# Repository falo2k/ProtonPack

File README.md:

# Teensy Based Proton Pack Electronics
This is my implementation of the electronics for a Ghostbusters Proton Pack.  It uses a Teensy microcontroller in both parts of the kit (Pack and Wand) and communicates between them over 4 wires (power + serial).  For now I have kept it to a simple movie implementation with some additions - overheating and music playback.  I've added two features that are a bit unusual:
- An OLED display in the rear box on the wand is used for managing volume control and track selection, in conjunctions with a rotary encoder (push/turn) in the front knob.
- A [bluetooth receiver](./Images/bluetooth.jpg) can be turned on for playback of anything not available on the SD card.  The module I'm using will mix the stereo audio down to mono for a single pack, but comes as a pair for True Wireless Stereo.  The other board will be in a friend's pack so we can use the packs as a complete speaker set.
  
It is designed to fit inside the 3D printed pack available [here - the Q-Pack](https://github.com/mr-kiou/q-pack).  It's been developed for a Mk3 pack - I will review it at some point in the future for Mk4 compatability.

## Software
The code is set up as a VS solution/project set using [Visual Micro](https://www.visualmicro.com/), but you can tweak this to your preferred environment.  There are three core files:
- Wand.ino for the Wand sketch
- Pack.ino for the Pack sketch
- ProtonPackCommon.h which is used by both for some shared enums, timers, etc.
  
The Wand sketch does all state management, and will update the Pack sketch as necessary over serial.  If you want to tweak speeds, animations, direction of switches, etc. then you should find the right data to change either above the setup() functions in each file, or within the common header.
  
You'll need the libraries listed in the section below.

### Libraries
[minIni for Arduino](https://github.com/lipoyang/minIni4Arduino) - Config file saving/loading with the SD card  
[LCDGFX](https://github.com/lexus2k/lcdgfx/) - Drives the OLED display  
[CmdMessenger](https://github.com/thijse/Arduino-CmdMessenger) - Manages serial connection between both boards with callbacks  
[Encoder](https://github.com/PaulStoffregen/Encoder) - Converts rotary encoder inputs to movement  
[HT16K33](https://github.com/jonpearse/ht16k33-arduino) - Basic library for controlling the LED matrix backpack/bargraph.  
[NeoPixel](https://github.com/adafruit/Adafruit_NeoPixel) - The Adafruit NeoPixel library.  Considered using FastLED, but as I had GRBW LEDs in stock (and wanted them for some parts) I stuck with the Adafruit library.  
[TimerEvent](https://github.com/cygig/TimerEvent) - A library for managing timing of updates (helping to banish unnecessary delay() calls)  
[Switch](https://github.com/avandalen/avdweb_Switch) - Primarily used for the debouncing and callback features for switches.  Detects events for pressing, holding, and releasing.  

### Pack Operation
Once power is on to both boards, they will start up in the state determined by the current switch positions, so you can switch straight into music mode if you want.  If the pack is powered without a wand connected, it will enter bluetooth mode after 5 seconds.  When both are connected, and the Activate switch is in the off position, a top light on the wand will pulse a faint blue to remind you that your battery is still connected!  

**Act Switch on Left Box**  
- This toggles the pack power-up for both movie and music mode.

**Lower Switch Next to Bargraph**  
- In movie mode this toggles whether or not the overheat warning will kick in after a period of time and then move to venting after further warning.  If off, firing will continue indefinitely.  
- In music mode, this is used to toggle the Bluetooth module on, which will then stop any playback from the SD card.

**Upper Switch Next to Bargraph**  
- This switches between movie mode (off) and music mode (on)

**Int Button on Left Box**  
- In movie mode, this will cause the pack to fire while held.  
- In music mode a single press will act as a play/pause button, while a long press will move to the next track in the list.

**Tip Button**  
- In movie mode, this will cause the pack to fire while held.  If single pressed, it will cause a venting routing to kick off.  
- In music mode a single press will act as a stop button, while a long press will move to the previous track in the list.

**Pack Crank Knob**  
- Connected to an encoder, this independently controls volume of the pack when held and turned.

**Pack Ion Switch**  
- Currently unused.

### OLED Menu System
A long press on the Wand encoder will activate the menu (to avoid accidental bumps).  While active, a long press will also cancel the menu.  The menu has an automatic timeout so will not stay open indefinitely.  Single click to select / confirm menu items

Currently there these features for control:  
1. **Volume**: This changes the volume of the amplifier in the pack via i2c.  This will update as you turn the knob.  
2. **Track Change**: This lets you select the extact track you want queued up for playback from the SD card (if enabled).  Single click to confirm the selection, or long press to cancel.  Selecting a new track while one is playing will cause the new track to start immediately.  Note that using the next/prev track shortcuts on the INT/TIP buttons will display the new track name in the display.  
3. **Overheat/Warning Time**: For overheat mode, this will change the timings for how long until the warning starts (overheat) and how long the warning lasts before forced venting (warning).  
4. **Load/Save Config**: This will load or save the volume, track, and timing configuration to a file on the SD card.  This is loaded as the default when the pack is first powered  
  
A long press in any menu item should take you back up one level.  
  
[Demo video here](https://youtu.be/a6icHuyzO3Q)
  
### Lights Colours & Lenses
The light colours I've used in my code were chosen to work with the lenses and printed hats I'm using.  I would recommend testing against your own installation and tweaking them accordingly.  My setup is:  
- Power cell is a layer of frosted acrylic + a top layer of blue acrylic (so lighting aims to send green and blue only)  
- Cyclotron lenses are just frosted acrylic so I can do any colour.  They are mounted over printed reflectors lined with a red chrome vinyl layer to give them a red tint when off.  
- For the wand LED covers the slo blo is red, tip hat is orange, front shelf is opaque white, top front is clear, and top rear is orange.  

### Future Plans
- General code refactoring where I've got a few inconsistent approaches.  Tidy up method signatures a bit to be consistent with ordering of arguments, remove TimerEvent as I've ended up with some custom implementations of the same principle so should be consistent.  
- Some pin headers in the pack are already spare to support adding a smoke machine to the pack at a later date for venting (marked as IO2 on the PCB).  This should be easy to add triggers in software at the appropriate state changes.  I've seen some interesting looking i2c relay boards or i2c IO expanders out there as alternative options if I want more granular control over pump, smoke, fan for the effects.  
- Alternative lighting schemes, sounds, animations, etc. can be added relatively easily.  Switching would probably be done with additional menu items through the OLED controls.  
- I'll play with adding more granular volume control, again through the menu, to individually tweak the volume of SFX, Music, and Bluetooth channels.  This may turn out to be unnnecessary given the sounds should already be balanced and bluetooth volume should be handled by the device sending audio.  
- The Ion Switch input currently doesn't do anything.  I may use this as either a hard or soft toggle for any future smoke effects.  
- Review the PCBs for other layout options.  Now I've got my own wiring in, I might see some better positioning for connectors, consider breakout boards, etc.  
- Consider either including an isolated converter in the BOM and as part of existing PCBs, or a breakout depending on power requirements for the smoke system.
- Consider a better menu system, and make **all** configurable settings switchable in software.  That would reduce the need for any trial and error with USB cables attached and would allow for all tweaking of things like switch directions, cyclotron spin directions, etc. possible through the OLED menu.  Could even then distribute just the binaries of the firmware for busters who don't want to go anywhere near an IDE.  
- I'd like to add USB panel breakouts onto the motherboard and somewhere on the wand for access to the internal devices without needing to take my shell off.  If I can somehow make the SD card accessible as mass storage when connected as well then so much the better. 

## Music Tracks
I've removed the music tracks from this repository, but you can see which ones I had loaded in [ProtonPackCommon.h](./Teensy/ProtonPackCommon/src/ProtonPackCommon.h).  You can replace these with your own copies, or adapt the header file to manage your own.  I used 16 bit 44.1khz wave files downmixed to mono as I only have a single speaker setup in the pack.  I believe the audio board does support MP3 with some overhead, but there's so much space on a SD card that I didn't care.  Audacity was used for file processing because it's great.  
  
If you want to add more music tracks to the pack, bearing in mind that it might take a while to change them given the simple scrolling menu, then you can update the arrays in ProtonPackCommon.h to reference them.  Make sure to update the track count as well.  
  
## Hardware
### BOM
Where I can remember it, I've listed the Equipment used and links to purchase below.  You may find other sources are better for availability (Mouser, Digikey, etc.).  As with all of these types of projects, it depends exactly how you're planning to mount your electronics, so I'd advise thinking about your layout before purchasing.  I'm assuming I don't need to go into tools and wire here, that should be a given.  A decent soldering iron is a must, and I have to say how much I'm loving my [Pinecil](https://www.pine64.org/pinecil/), and also the best helping hands I've ever used, the [Omnifixo](https://omnifixo.com/en-gb).  

**Controllers**  
 2 x [Teensy 4.0](https://www.pjrc.com/store/teensy40.html)  
 1 x [Teensy Audio Board Rev D](https://www.pjrc.com/store/teensy3_audio.html)  
 1 x [Teensy Stacking Header Kit](https://www.adafruit.com/product/3883).  For the audio board to stack on the Teensy 4.0.  This was the easiest source of 14 pin stackable headers I could find.  If not using PCBs then you may just stick with non-stacking headers here.  
 4 x [14x1R Pins](https://www.pjrc.com/store/header_14x1.html) for the Teensy boards  
 4 x [14x1R Socket Headers](https://www.pjrc.com/store/socket_14x1.html) for the PCBs  
 1 x [5x2R Socket Header](https://www.amazon.co.uk/Double-Female-Straight-Header-Socket-Black/dp/B00R1LKZOM/ref=sr_1_5?crid=2BQW1XCGHFEJU&keywords=2r+5+header&qid=1682349085&sprefix=2r+5+he%2Caps%2C120&sr=8-5) for the PCB connection to the audio inputs/outputs on the board  
 1 x Micro SD Card for the Audio Adapter.  See the [Audio Adapter product page](https://www.pjrc.com/store/teensy3_audio.html#:~:text=video%20for%20details.-,Recommended%20SD%20Card,-Most%20SD%20cards) for up to date recommendations.  Not much is stored on here so you can get away with a fairly small card, but if you want to load more songs on YMMV.  

**Premade Boards**  
1 x [Adafruit 16x8 LED Matrix Driver Backpack - HT16K33 Breakout](https://www.adafruit.com/product/1427) for driving the bargraph.  
1 x [DFRobot Mosfet Controller DFR0457](https://wiki.dfrobot.com/Gravity__MOSFET_Power_Controller_SKU__DFR0457) to switch the bluetooth board  
1 x [Adafruit 20W Class D Amplifier](https://www.adafruit.com/product/1752)  
1 x [Bluetooth Audio Board](https://www.aliexpress.com/item/1005004753541997.html). Comes as a wireless stereo pair.  

**Buttons and Switches**  
3 x [2 Position MTS102 mini toggle switches](https://www.amazon.co.uk/gp/product/B01BWL7Z44/) for wand  
1 x [Black Off/On SPST Momentary switch](https://www.amazon.co.uk/gp/product/B00TXNXU4S)  
1 x [Red Off/On SPST Momentary switch](https://www.amazon.co.uk/gp/product/B008ZYE9LY)  
2 x [EC11 Rotary Encoder with Switch](https://www.ebay.co.uk/sch/i.html?_from=R40&_trksid=p2380057.m570.l1313&_nkw=ec11+rotary+encoder&_sacat=0) for the pack (crank) and wand (top / front knob).  Lengths will depend on your shells, and where you're placing the encoder.  
  
Ion switches can be picked up on Etsy.  
  
I also use some of [these](https://www.digikey.co.uk/en/products/detail/e-switch/100DP1T1B1M1QEH/378867) to switch on/off and choose charging vs electronics power for my internally mounted [Talentcell battery](https://talentcell.com/lithium-ion-battery/12v/yb1206000-usb.html).

**LEDs**  
You may want to do your own LEDs.  Numbers and type can be varied in the code, though I haven't allowed for cyclotron LEDs that are more than a single addressable LED in a chain.  You may want to use the 7 LED jewels, though I found they were unnecessary for brightness and just ramped up power consumption for the sake of it.  
1 x [144LEDs/m SK6812 RGBW Strip](https://www.aliexpress.com/item/32476317187.html?spm=a2g0o.order_list.order_list_main.5.74871802yO2AMH).  144 LEDs/m is just enough density to give you 15 LEDs in the Power Cell.  You can get a minimum length if you like.  
13+ x [SK6812 RGBW Chips](https://www.aliexpress.com/item/1005002509850925.html?spm=a2g0o.order_list.order_list_main.29.74871802yO2AMH) which I use in the wand, pack vent, and for the cyclotron.  Worth getting some spares in case you fry one.  
1 x [RGBW LED jewel](https://www.aliexpress.com/item/32825068416.html?spm=a2g0o.order_list.order_list_main.56.74871802yO2AMH) for the barrel light  
1 x [28 Segment Bar Graph](http://www.barmeter.com/download/bl28-3005sda04y.pdf).  Sourcing for this always ends up out of date, so hunt around Aliexpress or try asking on one of the FB groups.  Note that there are two versions of this bargraph, a common anode and common cathode version.  My code is designed for the [BL28-3005SDK04Y](./Images/bargraphwiring.jpg) model (note the A or K in the model name differentiating them).  It can be adapted for the other by simply changing the array mapping in the common header to point to the correct row/column references for your model.  

**Capacitors and Resistors**  
4 x 4.7K Ohm Resistors for pullups on the Teensy i2c lines  
6 x 220 Ohm Resistors for neopixel data inputs  
2 x 100 uF Capacitors for neopixel power inputs (these may not be necessary depending on the pixels you're using - I'm keeping them in as they don't harm)  

**Connectors (for PCB / wiring)**  
Source these where you like depending on how many you need / want for other projects.  I tend to buy bulk lots from AliExpress.  You can count up the exact number you need, but I always find I need more so I'll leave them open ended :)  
- [JST-XH connectors and headers](https://www.digikey.co.uk/en/product-highlight/j/jst/xh-series-connectors) for the boards and cables (2,3,4 pin)  
- [Screw terminal blocks](https://www.digikey.co.uk/en/products/detail/phoenix-contact/1729018/260604) (2 pin, 5mm pitch) 
- [Dupont connectors](https://www.amazon.co.uk/dupont-connectors/s?k=dupont+connectors)
- [JST-SM wire to wire connectors](https://www.amazon.co.uk/Aussel-Connector-Housing-Assortment-Kit-560PCS-2-5mm-JST-SM-Connector-560PCS/dp/B0716JMHNJ/ref=sr_1_5?crid=1V0JLS666ZR6J&keywords=jst+sm+kit&qid=1682347520&sprefix=jst+sm+kit%2Caps%2C67&sr=8-5) for  (handy locking wire to wire options)  
- [JST-PH connectors](https://www.amazon.co.uk/RUNCCI-YUN-540Pcs-Connector-Housing-Adapter/dp/B092LWQJHN/ref=sr_1_7?crid=V8F2IT2RMUFS&keywords=jst%2Bph%2Bkit&qid=1682347555&sprefix=jst%2Bph%2Bkit%2Caps%2C65&sr=8-7&th=1) (2,3 pin) for some of the smaller connectors on the DFRobot boards and the bluetooth board  
- An assortment of [Wago221s](https://www.amazon.co.uk/s?k=wago+221) because they're brilliant for patching cables together with quick release  
- [2 Pairs of 4 pin aviation connectors](https://www.amazon.co.uk/gp/product/B09WXZNKXN/ref=ppx_yo_dt_b_search_asin_title?ie=UTF8&psc=1) which I use to carry the serial/power to and from the wand while allowing a quick release.

**Other**  
2 x [74AHCT125 Level Shifters](https://www.adafruit.com/product/1787) for driving the Neopixels as the Teensy uses 3.3V logic.  You may get away without these, but better safe than sorry.  
2 x [14 Pin IC Sockets](https://www.digikey.co.uk/en/products/detail/cnc-tech/245-14-1-03/3441580) for mounting the above into the PCBs (or you can just solder them in).  
1 x [0.91-inch OLED Display SSD1306](https://www.amazon.co.uk/gp/product/B07V8B3LSR)
1 x [M6 Thumb Nut](https://www.aliexpress.com/item/1005003320281166.html) for the top knob on the wand.  I drilled out a 2.5 mm hole in the side, tapped it for M3 and used a grub screw to attach it to an encoder.  The top is capped with a cut-off and glued countersunk bolt head.

### PCBs
I have created a couple of PCBs to make installation neater in a Q-Pack.  I've shared the production files in the PCBs folder for use with [JLCPCB](https://jlcpcb.com/) - note that they have a placeholder JLCJLCJLCJLC text on the rear silkscreen so you can use the "Specify a location" option in JLC for order numbering.  I used Altium Circuitmaker to create these, so it's hard to share a useful copy of them.  I plan at some point to migrate these to KiCad but that requires time to learn KiCad.  It'll probably happen when I start working on a better belt gizmo :)  
  
The folder also contains STLs to mount the boards and keep the solder joins clear of the mounting surface.  For the Wand, it is just a spacer - the board is designed to fit along the handle side of the Mk3 Q-Pack, using the external M3 bolt to secure it with a nut internally.  This should position the serial/power connections for the handle exit, but leave enough space for an encoder to run through the top/front knob if desired.  For the pack, it's a backer designed to have M3x5x4 heat sets (standard size used in [Vorons](https://www.vorondesign.com/)) added to the holes so the board can be attached and removed easily with M3 bolts.  The backer can then be secured in place to the motherboard with VHB tape.  It should be slim enough to fit underneath the booster box of the Mk3 Q-Pack.  

Lastly, the current version did not take into account the 3mm inset on the box lid.  I have added an alternative STL for this into the folder, but will refactor the PCBs when I redo them in the future.  My STL for the lid also changes some hole sizes as I'm using M3 + heat inserts to attach to the box, and M4 for metal V-Hook/S-Hook connectors.  

Note that the wand board already contains the components necessary for motor switching (transistor, diode, etc.), whereas the pack board offers simple HI/LO pin output for bluetooth and vent switching (with reference voltage).  This is to make it agnostic to how you want to do your switching for devices not directly powered by the Teensy.  If you don't want to build your own circuits, there are some good pre-packaged boards out there for relay switching or transistor switching.  DFRobot or Adafruit are good places to look.  

Note: Jigs - space for through hole components, but I wouldn't rely on them, or do them on a second pass.  They're often easier to do after the sockets, just bending the legs before soldering.  Jig accuracy will depend on how well tuned your printer is for dimensions, corners, etc. so some cleanup with a knife may be required if you wish to use them.  I find they fit snug (post any shrinkage) printing ABS on a Voron.

*Revision 1.0:* Initial release of boards  
*Revision 1.1:* Pack board updated to move Audio Board output pin.  I made a mis-reading of the schematic, and only the pins nearest the Teensy pins are connected to L/R out.  Temporarily solder bridged on my v1.0 boards.  
*Revision 2.0:* Wand board migrated to KiCad and updated to better fit in stock Q-Pack wand shell.  Updated the PCB to support the Teensy 4.0 as the LC is now EOL.  Added additional headers to board for USB data breakout (via pogo pins), for connecting a hall effect sensor for barrel state sensing, and for controlling a rumble motor (5V).  Generally re-jigged the layout, with the priority being having the teensy USB port facing upwards for access with the wand baseplate removed.

### Power
I've left supplying the 5V power to the boards to the individual user.  You can take a feed directly from a Talentcell 5V output or use a common buck converter, but either of these may introduce some noise into the audio.  Your mileage with this may vary.  I got myself some [isolated dc-dc converters](https://www.digikey.co.uk/en/products/detail/mornsun-america-llc/VRB1205S-6WR3/16348304) to step down my 12V talentcell battery and avoid noise issues going to the amp.  6W is overspecced - in my testing, the setup draws at most 0.6A at its busiest time when in the overheat warning sequence.  They're working [well for me so far](./Images/powerboard.jpg).

## Useful Models
I'm slowly going over my library of replacement parts and jigs that I've made over the course of this build and exporting them into the [STLs](./STLs/) folder (and where appropriate I'll feed some back as PRs for the q-pack).  Things like board mounts are generally reusable either with my PCBs or the off-the-shelf boards listed above.  Some bits I've made are very specific to my build so probably not of interest to others.  Have a play with Fusion 360 - you'll both love and hate yourself as a result, but you'll be too far down the rabbit hole of making to notice :)  

If you see any others I'm using in photos and want to get hold of them, let me know.  

## Thanks
A huge thanks to everyone over on the [Arduino for Ghostbusters Props](https://www.facebook.com/groups/1187612118706042/) Facebook group.  Special shout outs to:  
- Chris Rossi for steering me towards the Teensy in the first place
- Kevin Delcourt for his excellent github documentation.  Inspired me to take a different approach to fixing the top knob to the encoder!
- Quentin Machiels and Taco Belli over at [3D Printed Ghostbusters Props](https://www.facebook.com/groups/3DprintedGBprops/), without whom I would not have a pack to build this into
- [Mike Simone](https://github.com/MikeS11/ProtonPack) and [CountDeMonet](https://github.com/CountDeMonet/ArduinoProtonPack) for their implementations.  Both have steered hardware and software choices.

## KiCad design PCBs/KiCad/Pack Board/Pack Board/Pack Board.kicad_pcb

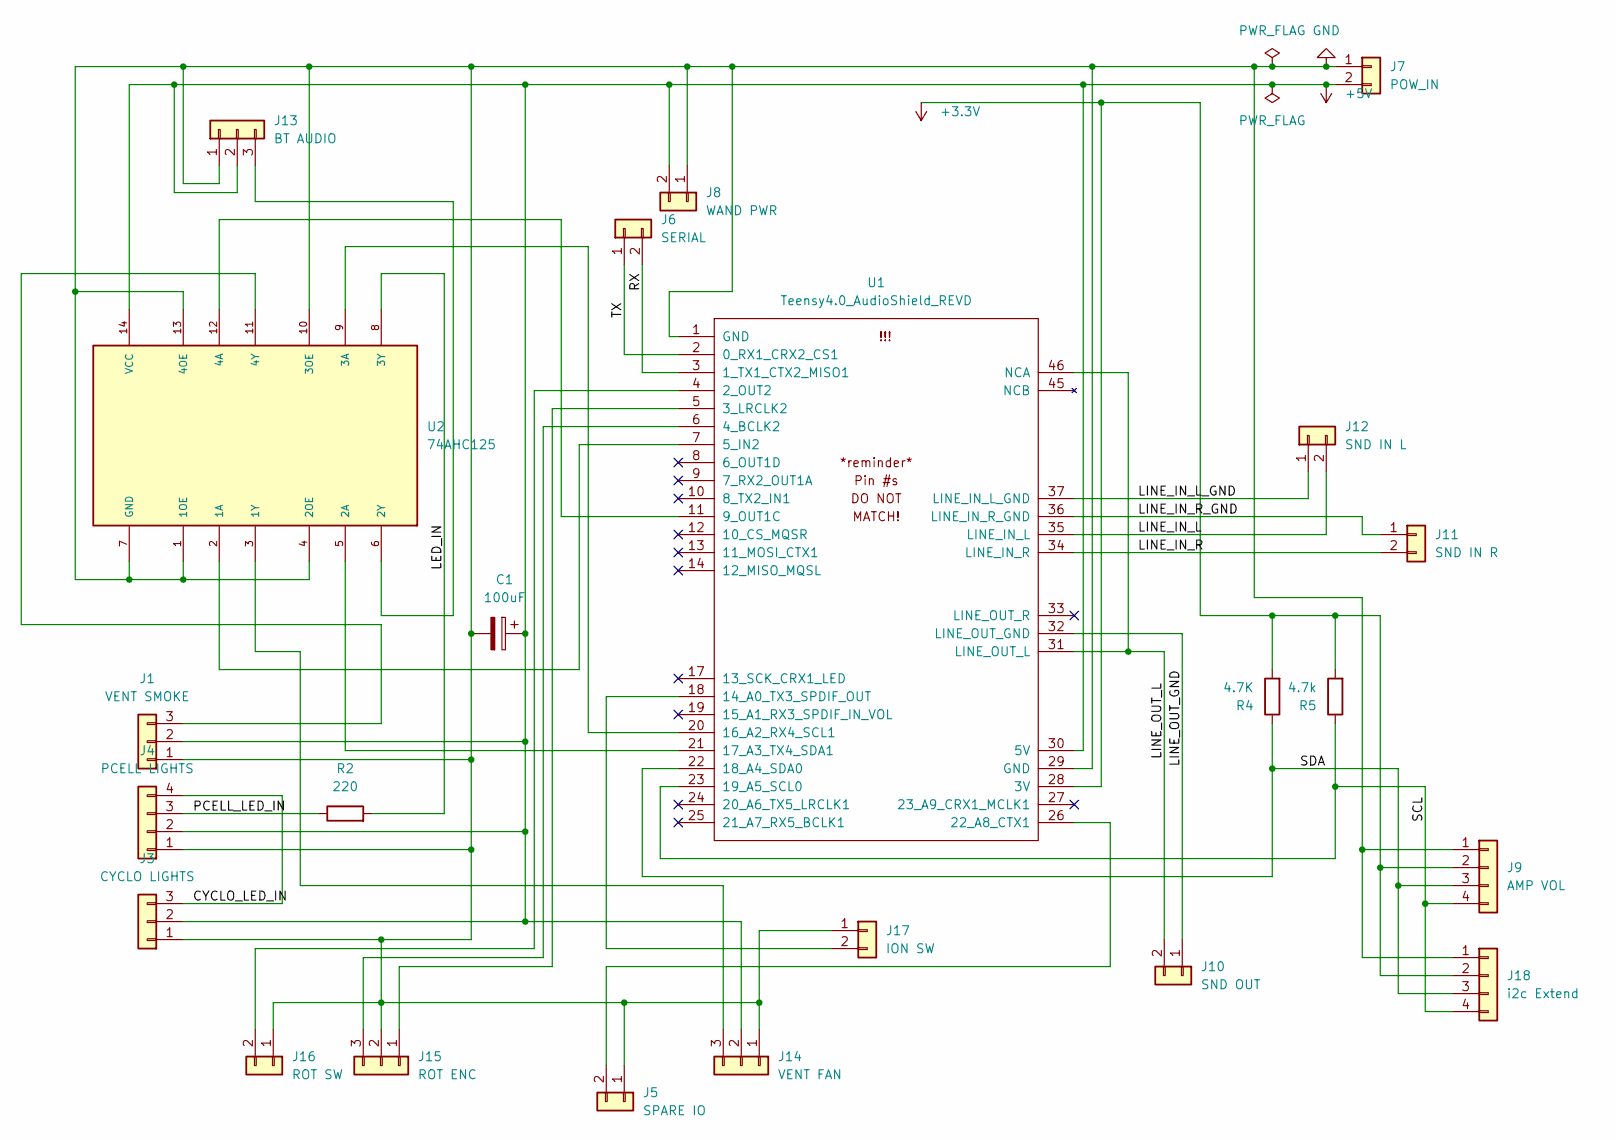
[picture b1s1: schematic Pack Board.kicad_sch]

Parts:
C1: 100uF; CP_Radial_D5.0mm_P2.00mm
J1: VENT SMOKE; JST_XH_B3B-XH-A_1x03_MosRelay
J3: CYCLO LIGHTS; JST_XH_B3B-XH-A_1x03_NeoPixelHeader
J4: PCELL LIGHTS; JST_XH_B4B-XH-A_1x04_NeoPixelHeader
J5: SPARE IO; JST_XH_B2B-XH-A_1x02_P2.50mm_Vertical
J6: SERIAL; TerminalBlock_Phoenix_MKDS-1,5-2_1x02_P5.00mm_Horizontal
J7: POW_IN; TerminalBlock_Phoenix_MKDS-1,5-2_1x02_P5.00mm_Horizontal
J8: WAND PWR; TerminalBlock_Phoenix_MKDS-1,5-2_1x02_P5.00mm_Horizontal
J9: AMP VOL; JST_XH_B4B-XH-A_1x04_i2cHeader
J10: SND OUT; JST_XH_B2B-XH-A_1x02_AudioHeader
J11: SND IN R; JST_XH_B2B-XH-A_1x02_AudioHeader
J12: SND IN L; JST_XH_B2B-XH-A_1x02_AudioHeader
J13: BT AUDIO; JST_XH_B3B-XH-A_1x03_MosRelay
J14: VENT FAN; JST_XH_B3B-XH-A_1x03_MosRelay
J15: ROT ENC; JST_XH_B3B-XH-A_1x03_RotEncoder
J16: ROT SW; JST_XH_B2B-XH-A_1x02_P2.50mm_Vertical
J17: ION SW; JST_XH_B2B-XH-A_1x02_P2.50mm_Vertical
J18: i2c Extend; JST_XH_B4B-XH-A_1x04_i2cHeader
R2: 220; R_Axial_DIN0207_L6.3mm_D2.5mm_P7.62mm_Horizontal
R4: 4.7K; R_Axial_DIN0207_L6.3mm_D2.5mm_P7.62mm_Horizontal
R5: 4.7k; R_Axial_DIN0207_L6.3mm_D2.5mm_P7.62mm_Horizontal
U1: Teensy4.0_AudioShield_REVD; Teensy Audioshield Rev D
U2: 74AHC125; DIP-14_W7.62mm_Socket

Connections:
+3.3V: J9.2, J18.2, R4.2, R5.2, U1.28 (3V)
+5V: C1.1, J1.2, J3.2, J4.2, J7.2, J8.2, J13.2, J14.2, U1.30 (5V), U2.14 (VCC)
/CYCLO_LED_IN: J3.3, J4.4
/LED_IN: R2.2, U2.8 (3Y)
/LINE_IN_L: J12.2, U1.35 (LINE_IN_L)
/LINE_IN_L_GND: J12.1, U1.37 (LINE_IN_L_GND)
/LINE_IN_R: J11.2, U1.34 (LINE_IN_R)
/LINE_IN_R_GND: J11.1, U1.36 (LINE_IN_R_GND)
/LINE_OUT_GND: J10.1, U1.32 (LINE_OUT_GND)
/LINE_OUT_L: J10.2, U1.31 (LINE_OUT_L), U1.46 (NCA)
/PCELL_LED_IN: J4.3, R2.1
/RX: J6.2, U1.3 (1_TX1_CTX2_MISO1)
/SCL: J9.4, J18.4, R5.1, U1.23 (19_A5_SCL0)
/SDA: J9.3, J18.3, R4.1, U1.22 (18_A4_SDA0)
/TX: J6.1, U1.2 (0_RX1_CRX2_CS1)
GND: C1.2, J1.1, J3.1, J4.1, J5.1, J7.1, J8.1, J9.1, J13.1, J14.1, J15.2, J16.1, J17.1, J18.1, U1.1 (GND), U1.29 (GND), U2.1 (1OE), U2.4 (2OE), U2.7 (GND), U2.10 (3OE), U2.13 (4OE)
unnamed: J1.3, U2.11 (4Y)
unnamed: J5.2, U1.26 (22_A8_CTX1)
unnamed: J13.3, U2.6 (2Y)
unnamed: J14.3, U2.3 (1Y)
unnamed: J15.1, U1.5 (3_LRCLK2)
unnamed: J15.3, U1.6 (4_BCLK2)
unnamed: J16.2, U1.4 (2_OUT2)
unnamed: J17.2, U1.18 (14_A0_TX3_SPDIF_OUT)
unnamed: U1.7 (5_IN2), U2.2 (1A)
unnamed: U1.11 (9_OUT1C), U2.12 (4A)
unnamed: U1.20 (16_A2_RX4_SCL1), U2.9 (3A)
unnamed: U1.21 (17_A3_TX4_SDA1), U2.5 (2A)

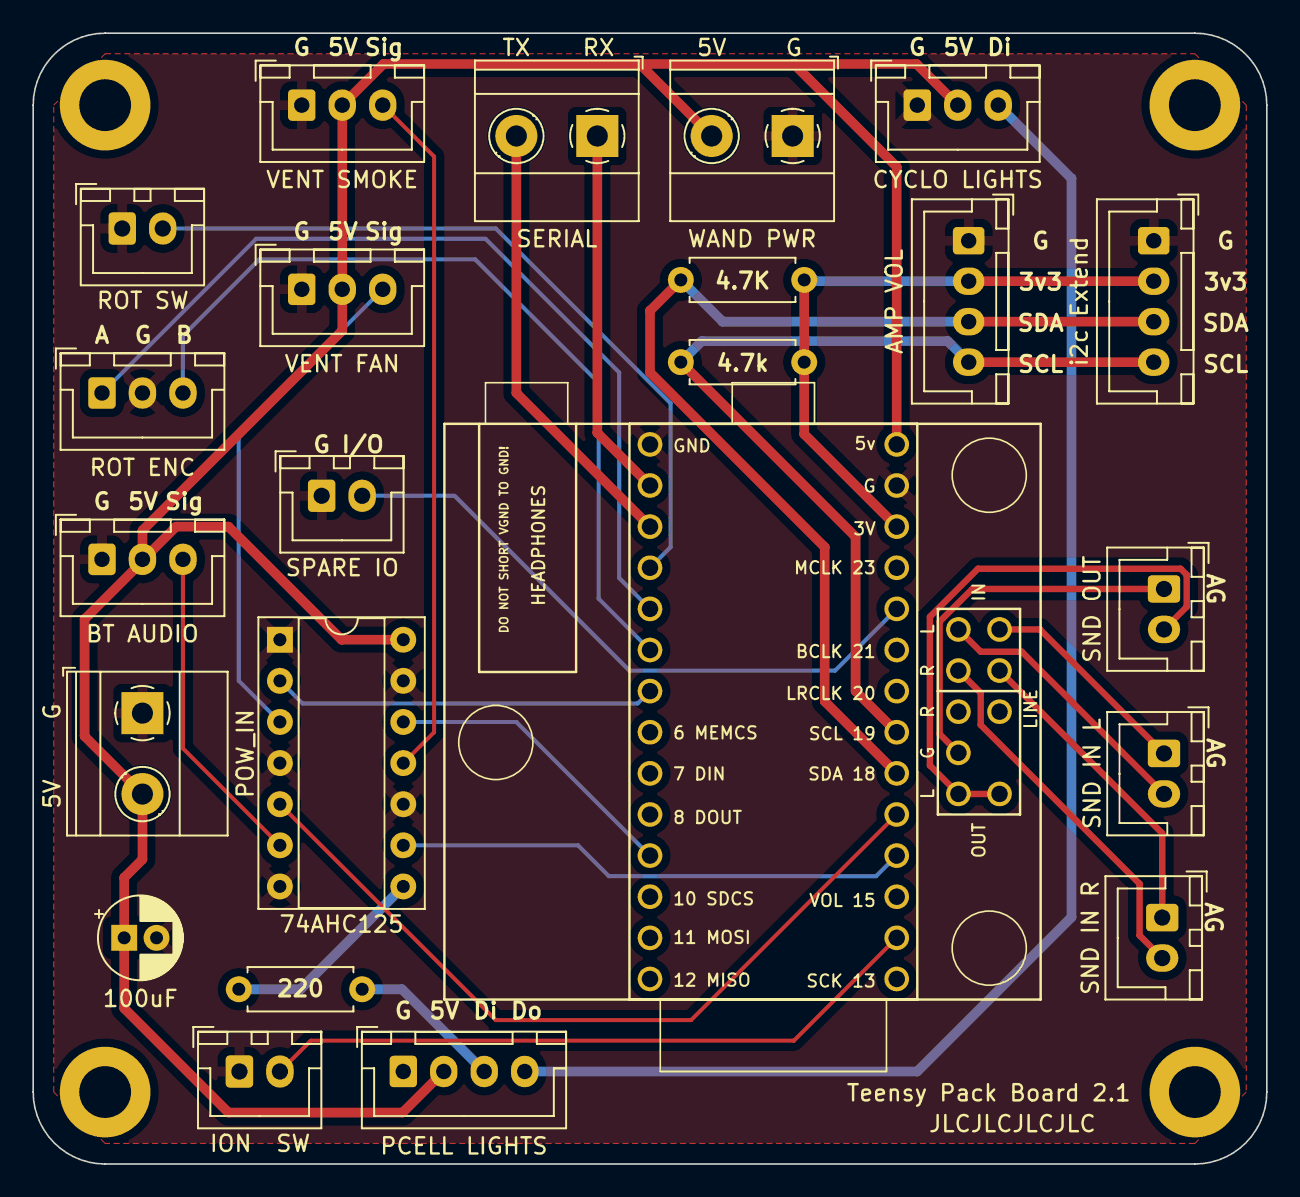
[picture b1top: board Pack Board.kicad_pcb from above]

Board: 2 copper layers, 76.2 x 69.8 mm, 23 parts (0 on the bottom side), 28 nets.

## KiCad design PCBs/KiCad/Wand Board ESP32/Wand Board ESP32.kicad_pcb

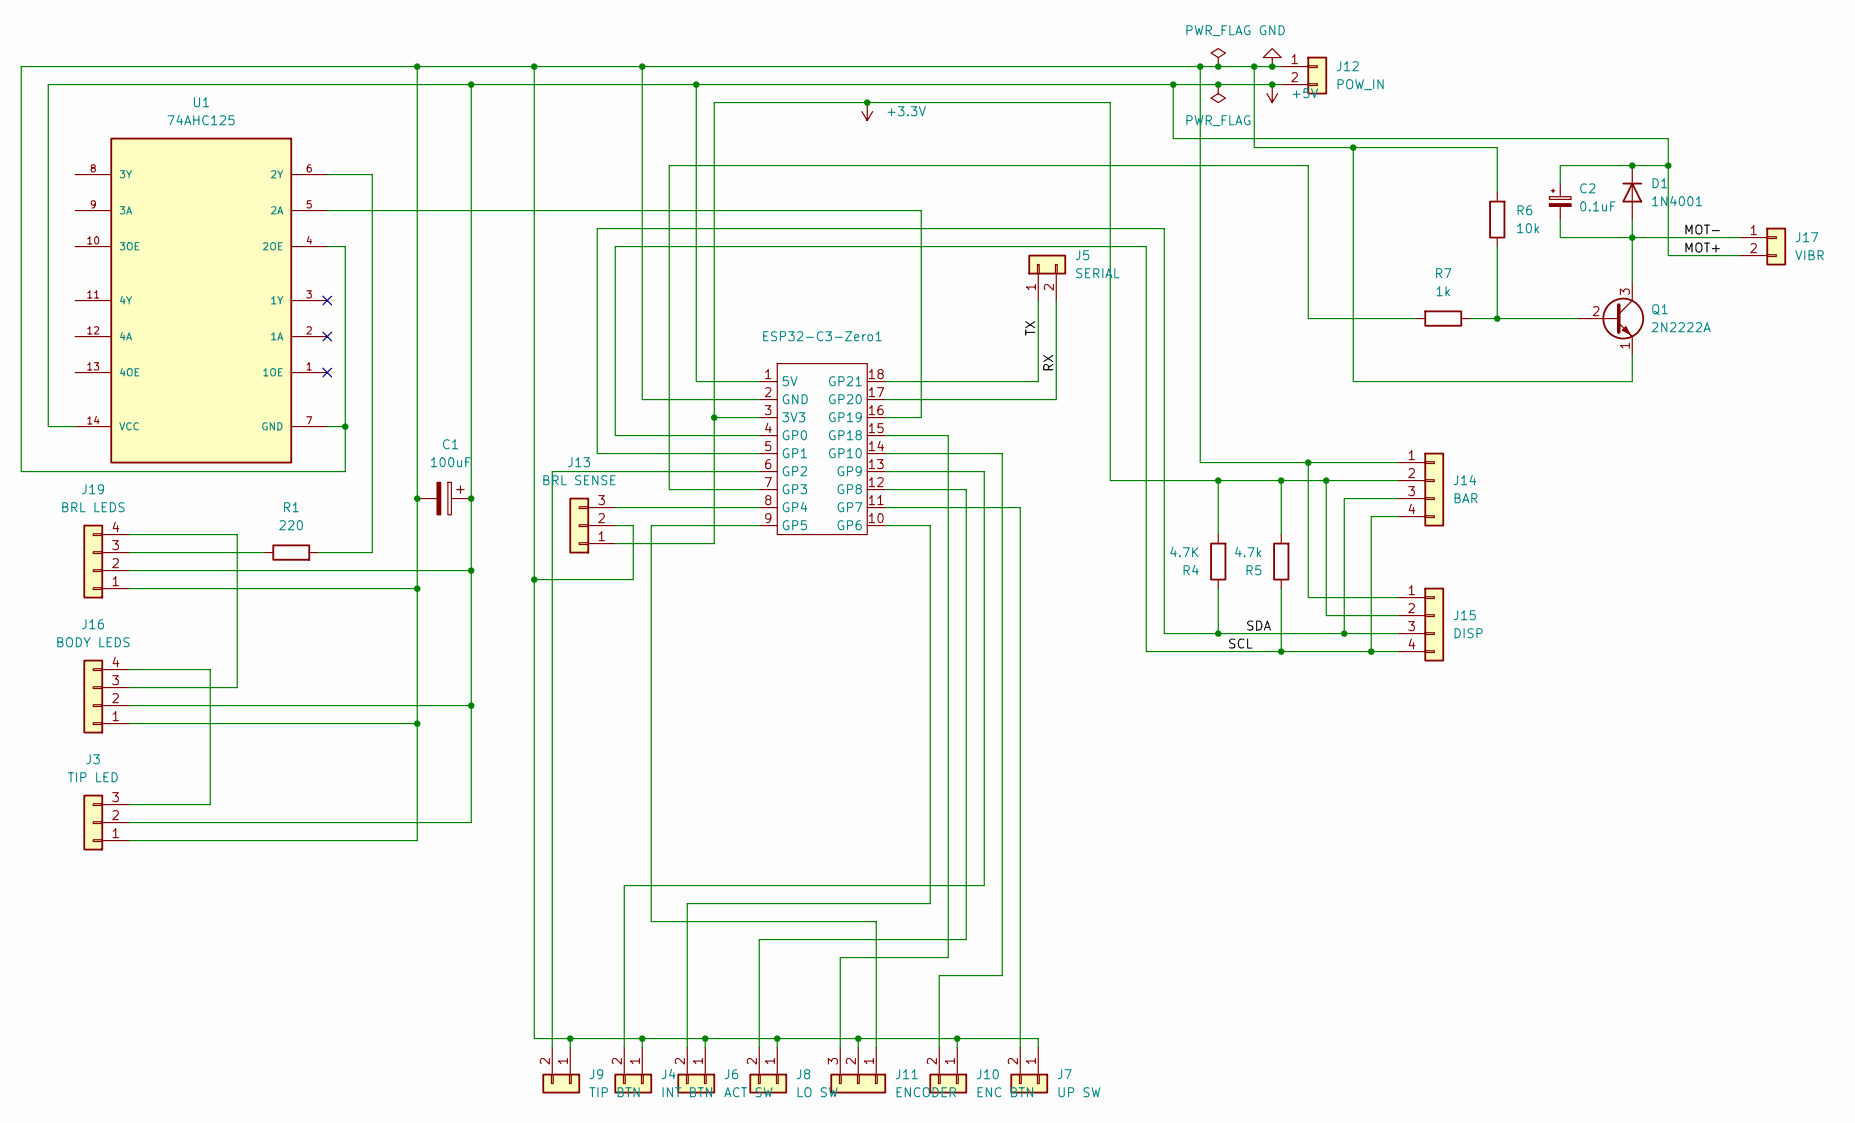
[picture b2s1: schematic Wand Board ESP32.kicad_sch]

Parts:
C1: 100uF; CP_Radial_D5.0mm_P2.00mm
C2: 0.1uF; CP_Radial_D4.0mm_P2.00mm
D1: 1N4001; D_DO-41_SOD81_P10.16mm_Horizontal
ESP32-C3-Zero1: ESP32-C3-Zero
J3: TIP LED; JST_XH_B3B-XH-A_1x03_NeoPixelHeader
J4: INT BTN; JST_XH_B2B-XH-A_1x02_P2.50mm_Vertical
J5: SERIAL; TerminalBlock_Phoenix_MKDS-1,5-2_1x02_P5.00mm_Horizontal
J6: ACT SW; JST_XH_B2B-XH-A_1x02_P2.50mm_Vertical
J7: UP SW; JST_XH_B2B-XH-A_1x02_P2.50mm_Vertical
J8: LO SW; JST_XH_B2B-XH-A_1x02_P2.50mm_Vertical
J9: TIP BTN; JST_XH_B2B-XH-A_1x02_P2.50mm_Vertical
J10: ENC BTN; JST_XH_B2B-XH-A_1x02_P2.50mm_Vertical
J11: ENCODER; JST_XH_B3B-XH-A_1x03_P2.50mm_Vertical
J12: POW_IN; TerminalBlock_Phoenix_MKDS-1,5-2_1x02_P5.00mm_Horizontal
J13: BRL SENSE; JST_XH_B3B-XH-A_1x03_P2.50mm_Vertical
J14: BAR; JST_XH_B4B-XH-A_1x04_P2.50mm_Vertical
J15: DISP; JST_XH_B4B-XH-A_1x04_P2.50mm_Vertical
J16: BODY LEDS; JST_XH_B4B-XH-A_1x04_NeoPixelHeader
J17: VIBR; JST_XH_B2B-XH-A_1x02_P2.50mm_Vertical
J19: BRL LEDS; JST_XH_B4B-XH-A_1x04_NeoPixelHeader
Q1: 2N2222A; TO-92_Inline
R1: 220; R_Axial_DIN0207_L6.3mm_D2.5mm_P7.62mm_Horizontal
R4: 4.7K; R_Axial_DIN0207_L6.3mm_D2.5mm_P7.62mm_Horizontal
R5: 4.7k; R_Axial_DIN0207_L6.3mm_D2.5mm_P7.62mm_Horizontal
R6: 10k; R_Axial_DIN0207_L6.3mm_D2.5mm_P7.62mm_Horizontal
R7: 1k; R_Axial_DIN0207_L6.3mm_D2.5mm_P7.62mm_Horizontal
U1: 74AHC125; DIP-14_W7.62mm_Socket

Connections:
+3.3V: ESP32-C3-Zero1.3 (3V3), J13.1, J14.2, J15.2, R4.2, R5.2
+5V: C1.1, C2.1, D1.1 (K), ESP32-C3-Zero1.1 (5V), J3.2, J12.2, J16.2, J17.2, J19.2, U1.14 (VCC)
/MOT-: C2.2, D1.2 (A), J17.1, Q1.3 (C)
/RX: ESP32-C3-Zero1.17 (GP20), J5.2
/SCL: ESP32-C3-Zero1.4 (GP0), J14.4, J15.4, R5.1
/SDA: ESP32-C3-Zero1.5 (GP1), J14.3, J15.3, R4.1
/TX: ESP32-C3-Zero1.18 (GP21), J5.1
GND: C1.2, ESP32-C3-Zero1.2 (GND), J3.1, J4.1, J6.1, J7.1, J8.1, J9.1, J10.1, J11.2, J12.1, J13.2, J14.1, J15.1, J16.1, J19.1, Q1.1 (E), R6.2, U1.4 (2OE), U1.7 (GND)
unnamed: ESP32-C3-Zero1.6 (GP2), J9.2
unnamed: ESP32-C3-Zero1.7 (GP3), R7.2
unnamed: ESP32-C3-Zero1.8 (GP4), J13.3
unnamed: ESP32-C3-Zero1.9 (GP5), J11.1
unnamed: ESP32-C3-Zero1.10 (GP6), J6.2
unnamed: ESP32-C3-Zero1.11 (GP7), J7.2
unnamed: ESP32-C3-Zero1.12 (GP8), J8.2
unnamed: ESP32-C3-Zero1.13 (GP9), J4.2
unnamed: ESP32-C3-Zero1.14 (GP10), J10.2
unnamed: ESP32-C3-Zero1.15 (GP18), J11.3
unnamed: ESP32-C3-Zero1.16 (GP19), U1.5 (2A)
unnamed: J16.3, J19.4
unnamed: J3.3, J16.4
unnamed: J19.3, R1.1
unnamed: Q1.2 (B), R6.1, R7.1
unnamed: R1.2, U1.6 (2Y)

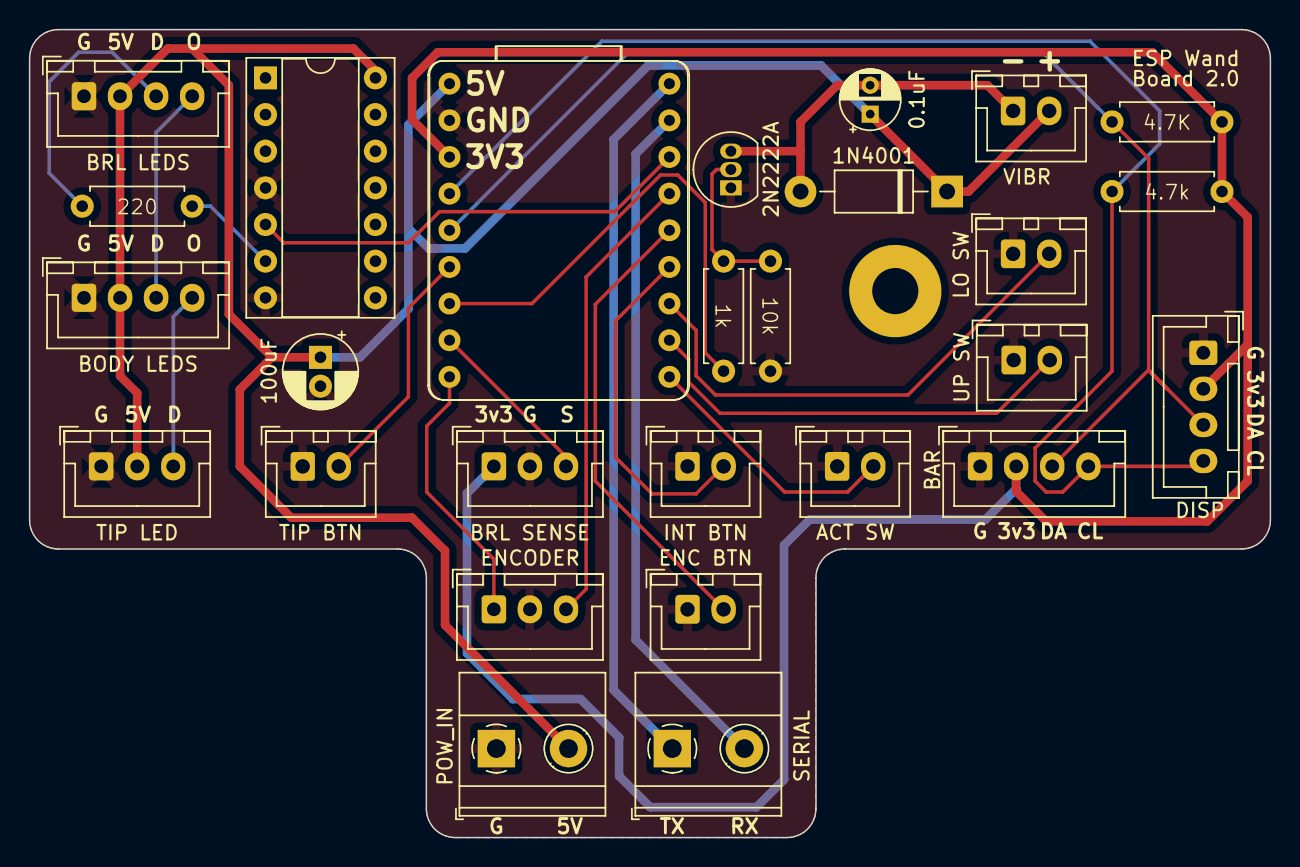
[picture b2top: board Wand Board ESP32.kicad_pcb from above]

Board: 2 copper layers, 86.0 x 56.0 mm, 27 parts (0 on the bottom side), 24 nets.

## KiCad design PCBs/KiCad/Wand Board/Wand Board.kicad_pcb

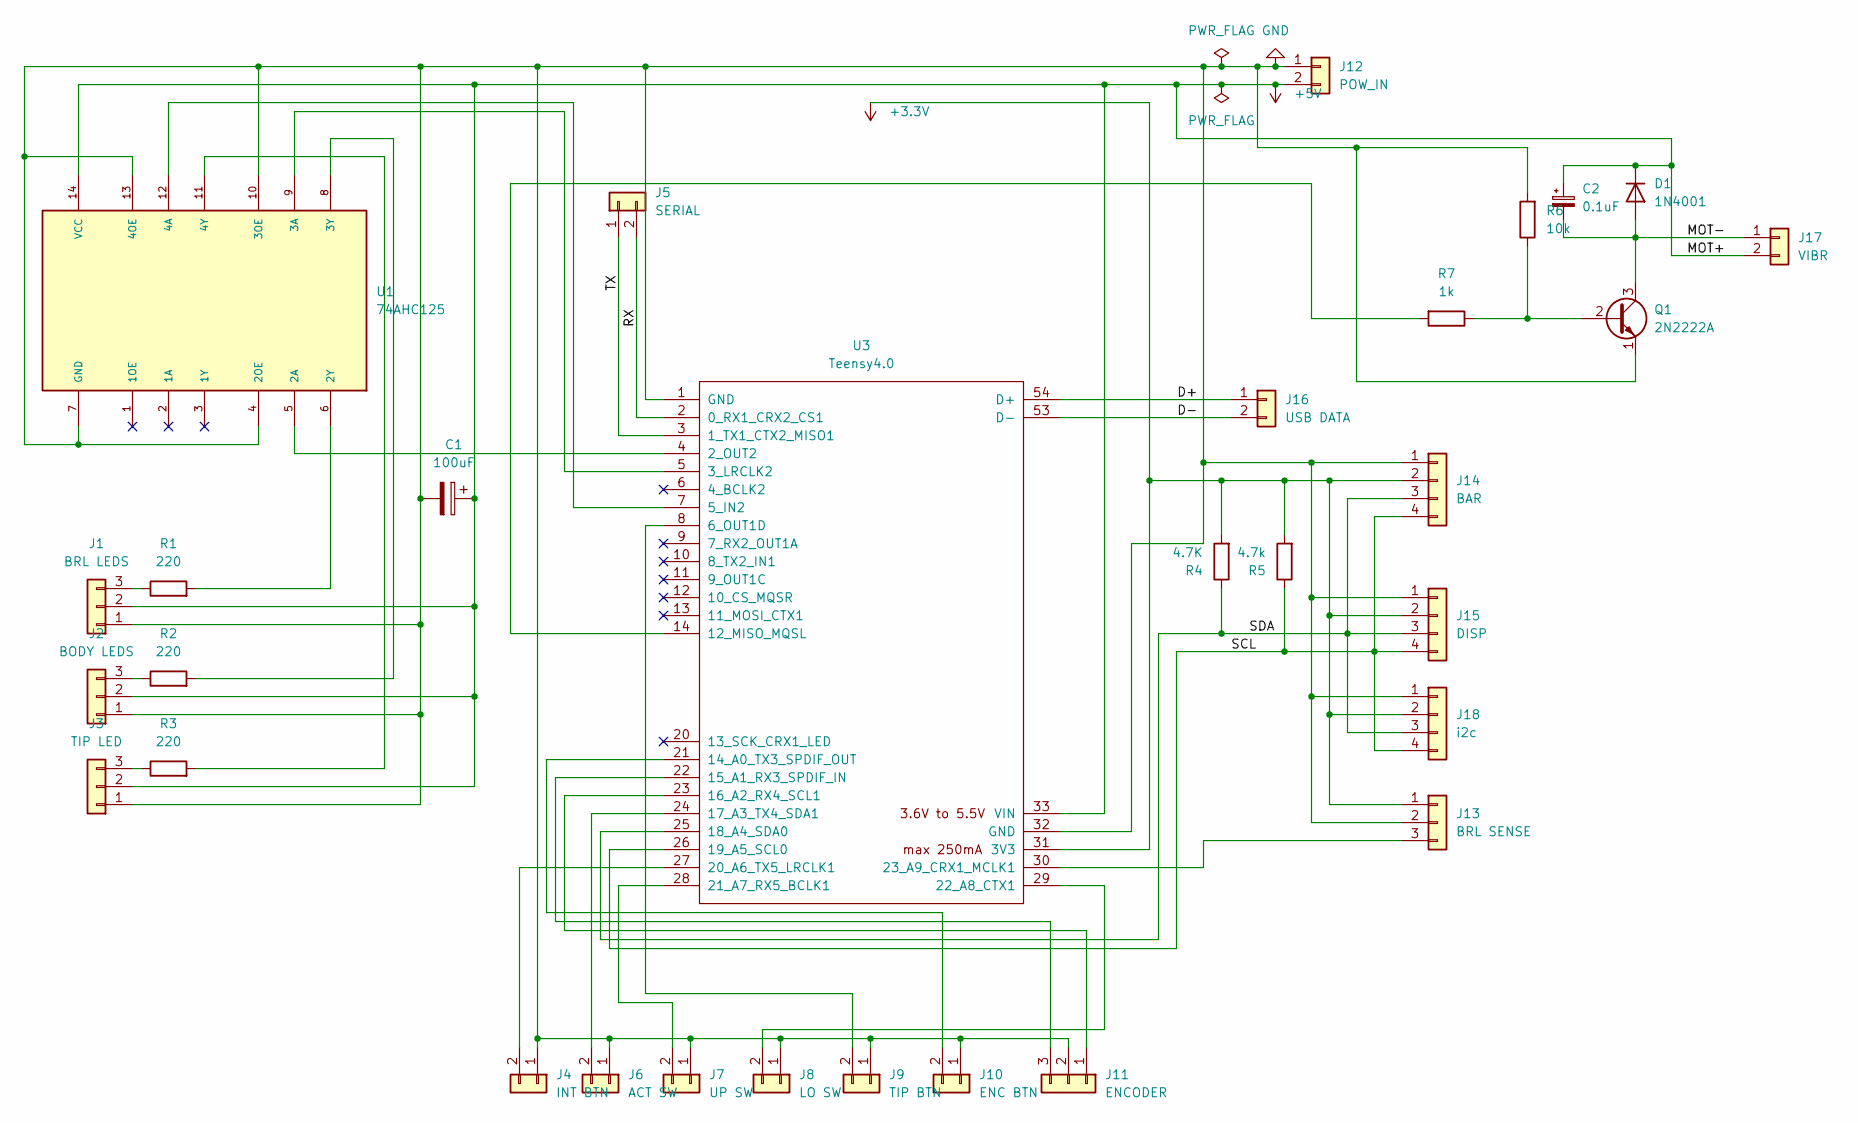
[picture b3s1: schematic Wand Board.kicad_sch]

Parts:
C1: 100uF; CP_Radial_D5.0mm_P2.00mm
C2: 0.1uF; CP_Radial_D4.0mm_P2.00mm
D1: 1N4001; D_DO-41_SOD81_P10.16mm_Horizontal
J1: BRL LEDS; JST_XH_B3B-XH-A_1x03_NeoPixelHeader
J2: BODY LEDS; JST_XH_B3B-XH-A_1x03_NeoPixelHeader
J3: TIP LED; JST_XH_B3B-XH-A_1x03_NeoPixelHeader
J4: INT BTN; JST_XH_B2B-XH-A_1x02_P2.50mm_Vertical
J5: SERIAL; TerminalBlock_Phoenix_MKDS-1,5-2_1x02_P5.00mm_Horizontal
J6: ACT SW; JST_XH_B2B-XH-A_1x02_P2.50mm_Vertical
J7: UP SW; JST_XH_B2B-XH-A_1x02_P2.50mm_Vertical
J8: LO SW; JST_XH_B2B-XH-A_1x02_P2.50mm_Vertical
J9: TIP BTN; JST_XH_B2B-XH-A_1x02_P2.50mm_Vertical
J10: ENC BTN; JST_XH_B2B-XH-A_1x02_P2.50mm_Vertical
J11: ENCODER; JST_XH_B3B-XH-A_1x03_P2.50mm_Vertical
J12: POW_IN; TerminalBlock_Phoenix_MKDS-1,5-2_1x02_P5.00mm_Horizontal
J13: BRL SENSE; JST_XH_B3B-XH-A_1x03_P2.50mm_Vertical
J14: BAR; JST_XH_B4B-XH-A_1x04_P2.50mm_Vertical
J15: DISP; JST_XH_B4B-XH-A_1x04_P2.50mm_Vertical
J16: USB DATA; JST_XH_B2B-XH-A_1x02_P2.50mm_Vertical
J17: VIBR; JST_XH_B2B-XH-A_1x02_P2.50mm_Vertical
J18: i2c; JST_XH_B4B-XH-A_1x04_P2.50mm_Vertical
Q1: 2N2222A; TO-92_Inline
R1, R2, R3: 220; R_Axial_DIN0207_L6.3mm_D2.5mm_P7.62mm_Horizontal
R4: 4.7K; R_Axial_DIN0207_L6.3mm_D2.5mm_P7.62mm_Horizontal
R5: 4.7k; R_Axial_DIN0207_L6.3mm_D2.5mm_P7.62mm_Horizontal
R6: 10k; R_Axial_DIN0207_L6.3mm_D2.5mm_P7.62mm_Horizontal
R7: 1k; R_Axial_DIN0207_L6.3mm_D2.5mm_P7.62mm_Horizontal
U1: 74AHC125; DIP-14_W7.62mm_Socket
U3: Teensy4.0; Teensy40-DHolesOnly

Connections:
+3.3V: J13.1, J14.2, J15.2, J18.2, R4.2, R5.2, U3.31 (3V3)
+5V: C1.1, C2.1, D1.1 (K), J1.2, J2.2, J3.2, J12.2, J17.2, U1.14 (VCC), U3.33 (VIN)
/D+: J16.1, U3.54 (D+)
/D-: J16.2, U3.53 (D-)
/MOT-: C2.2, D1.2 (A), J17.1, Q1.3 (C)
/RX: J5.2, U3.2 (0_RX1_CRX2_CS1)
/SCL: J14.4, J15.4, J18.4, R5.1, U3.26 (19_A5_SCL0)
/SDA: J14.3, J15.3, J18.3, R4.1, U3.25 (18_A4_SDA0)
/TX: J5.1, U3.3 (1_TX1_CTX2_MISO1)
GND: C1.2, J1.1, J2.1, J3.1, J4.1, J6.1, J7.1, J8.1, J9.1, J10.1, J11.2, J12.1, J13.2, J14.1, J15.1, J18.1, Q1.1 (E), R6.2, U1.4 (2OE), U1.7 (GND), U1.10 (3OE), U1.13 (4OE), U3.1 (GND), U3.32 (GND)
unnamed: J1.3, R1.1
unnamed: J2.3, R2.1
unnamed: J3.3, R3.1
unnamed: J4.2, U3.27 (20_A6_TX5_LRCLK1)
unnamed: J6.2, U3.24 (17_A3_TX4_SDA1)
unnamed: J7.2, U3.28 (21_A7_RX5_BCLK1)
unnamed: J8.2, U3.29 (22_A8_CTX1)
unnamed: J9.2, U3.8 (6_OUT1D)
unnamed: J10.2, U3.21 (14_A0_TX3_SPDIF_OUT)
unnamed: J11.1, U3.23 (16_A2_RX4_SCL1)
unnamed: J11.3, U3.22 (15_A1_RX3_SPDIF_IN)
unnamed: J13.3, U3.30 (23_A9_CRX1_MCLK1)
unnamed: Q1.2 (B), R6.1, R7.1
unnamed: U1.5 (2A), U3.4 (2_OUT2)
unnamed: R1.2, U1.6 (2Y)
unnamed: U1.9 (3A), U3.5 (3_LRCLK2)
unnamed: R2.2, U1.8 (3Y)
unnamed: U1.12 (4A), U3.7 (5_IN2)
unnamed: R3.2, U1.11 (4Y)
unnamed: R7.2, U3.14 (12_MISO_MQSL)

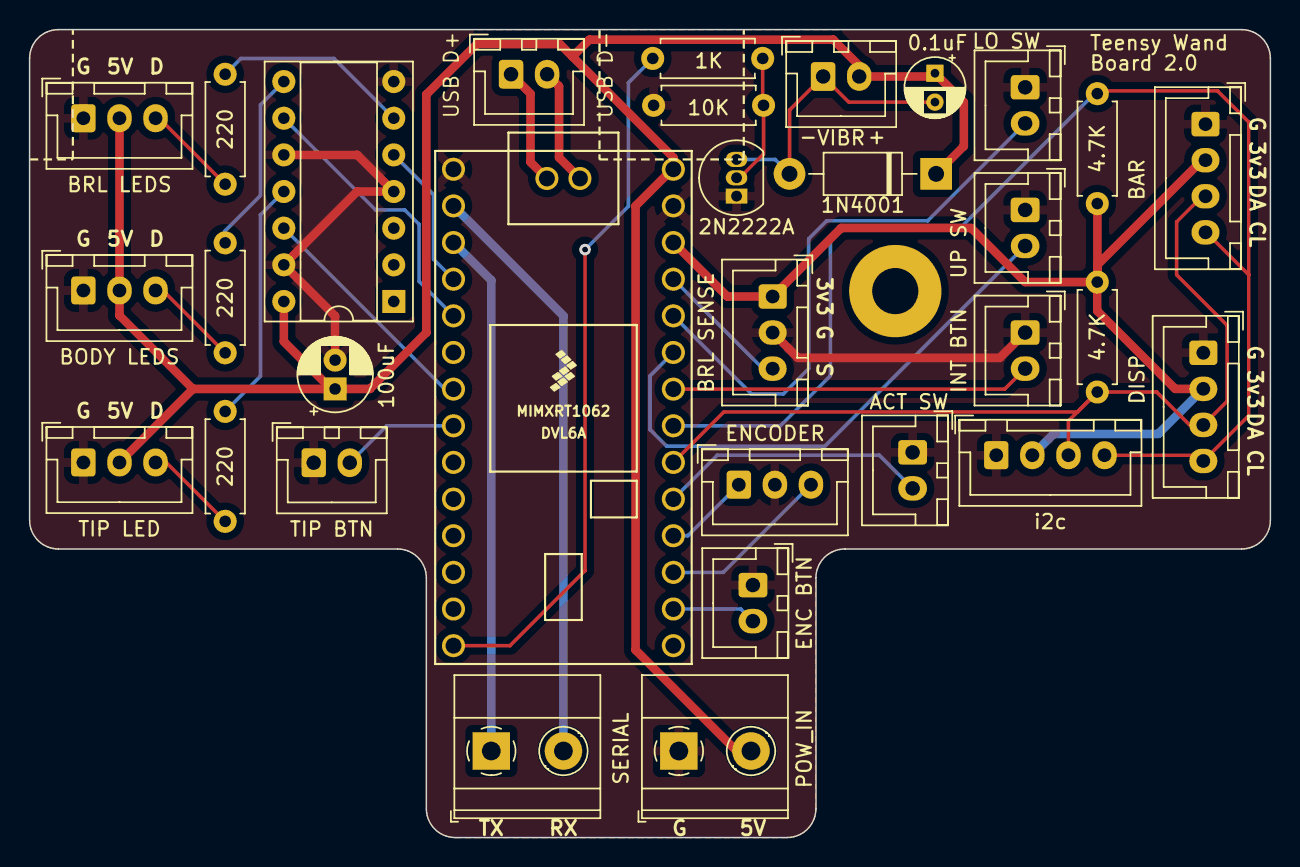
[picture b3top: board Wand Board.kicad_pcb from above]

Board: 2 copper layers, 86.0 x 56.0 mm, 31 parts (0 on the bottom side), 30 nets.

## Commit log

2022-07-25 Initial Version
2022-07-26 Pin definitions
2022-07-26 Basic state management for switches
2022-07-28 Audio Switching On Sliders
2022-08-01 Basic pack animations
2023-01-13 Tidying up
2023-01-13 Audio files initial setup for Teensy deployment
2023-01-13 Project setup for Teensy
2023-01-15 Project setups, libraries, and tests
2023-01-15 Moved audio files
2023-01-15 Basic Button Handling
2023-02-26 Updated PIN definitions to match PCBs
2023-03-10 Cleaned up pack code
2023-03-10 Audio Structure
2023-03-26 Switches for Wand
2023-04-04 Menu system for wand
2023-04-06 Wand event handlers for serial, button handling
2023-04-06 Removed old text file used for notes!
2023-04-07 State changes and initialisation
2023-04-07 Video Game Audio Files Added
2023-04-07 Downmix to mono
2023-04-08 Serial comms between wand and pack
2023-04-08 Booting animations for Power Cell
2023-04-09 Cyclotron animations for idle and firing
2023-04-09 Audio implemented and basic venting animation
2023-04-09 Bluetooth toggle
2023-04-10 Audio naming tweaks, fix to indexing on power cell, new music mode pack effects
2023-04-10 Firing animation
2023-04-10 Wand body and tip lights
2023-04-12 Gamme correction for colour transitions to make them smoother
2023-04-12 Fixed pack transitions to idle from firing stop, and 5xslowdown to firing stop
2023-04-12 Fix to flash on vent (had multiplier backwards)
2023-04-12 Fix to cyclotron transition from boot to idle to avoid instant off of lamps
2023-04-12 Moved displaystates enum definition to common header to get rid of annoying intellisense error
2023-04-12 Removed some leftover debug messaging that was causing noise
2023-04-12 Drive cyclotron music mode with HSV rather than Green,Yellow,Red
2023-04-12 Power Cell Music Mode tweaks - colour distribution, multipliers, min/max
2023-04-12 Music modes cleanup and tweaks for FFT
2023-04-12 Changed powercell routine to go to full blank when scrolling. Added booting animation for bargraph
2023-04-12 Basic bargraph animations complete
2023-04-13 Started fleshing out documentation
2023-04-13 Cleaned up some bargraph functions, moved writing out of clear to make calls to write explicit as needed
2023-04-13 Implemented config load/save
2023-04-13 Documentation: Some placeholders left in BOM
2023-04-13 PCBs
2023-04-13 Documentation layout tweaks
2023-04-13 Removed old Bounce 2 reference
2023-04-14 Donation buttons for github
2023-04-14 Buttons on README.md
2023-04-24 Readme updates
2023-04-24 Added default bluetooth demo mode for pack when not connected to wand
2023-04-24 Updated README.md and added folder for STLs
2023-04-24 More STLs
2023-04-24 STL fixes
2023-04-24 Finished the BOM (as much as I cba to right now)
2023-04-24 I hate markdown
2023-04-30 README.md update
2023-04-30 Changelog
2023-05-02 Notes on LED lenses
2023-05-06 Changed LED colours to match lens shades. Added default volume load to Bluetooth idle mode. Changed pack knob to control volume when held. Reduced maximum powercell index so it will always show a bit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
2023-05-06 Blinking warning light and flickering vent on warning.
2023-05-06 Made battery on indicator pulse
2023-05-06 Right justify display text. Stop initial volume updates causing display to show
2023-05-06 Added ability to customise the overheat/warning times, and lowered the default setting. This setting can be saved to SD.
2023-05-07 Updated README.md with 1.1 notes
2023-05-07 Changelog and photos
2023-05-07 Zoom pack PCB photo
2023-05-13 Updates to audio (removal from repo) and addition of license.
2023-05-13 Ignore file to avoid re-uploading music tracks
2023-05-13 Added PCB schematic printouts as interim until I can remake PCBs in a more open application
2023-05-13 Added to-do list items
2023-05-20 Readme and picture tweaks.
2023-05-20 Demo Video Uploaded
2023-05-20 Menu demo video
2023-05-20 Fixing some README typos / word choices
2023-05-20 A slightly modified rear box lid which really pushes where you can fit the 128x32 OLED as much to the right as possible without changing the existing rear box design.
2023-05-20 Base plate modified for current PCBs - future versions should make unnecessary. Adjust holes to suit your own needs
2023-06-13 Beginning to segregate hardware and software config into separate headers to preserve user changes over updates
2023-08-18 Wand Board 2.0 KiCad
2023-08-20 Gerbers and STEP for Wand Board 2.0
2023-10-09 Wand Board Updates
2023-10-18 Updated Wand Board PCB: Migrate to Teensy 4.0, Change Encoder Pin Order
2023-10-20 Added motor output for wand rumble
2023-12-09 Added additional i2c output to wand board for optional driver
2023-12-09 Pack Board 2.0
2023-12-19 Fixed Gerbers for extended i2c wand board. Exported STEP files of boards for jig creation.
2023-12-19 Soldering jigs for PCBs, updated schematic printouts
2024-07-03 Initial Platform IO Setup with ESP32-C3 in wand
2024-07-03 Updated PCBs for ESP32 Wand Build
2024-07-03 Removed old Teensy build files
2024-07-03 Remove old Wand PCB design
2024-07-04 Step file exports of boards
2024-07-06 Update README.md
    Fixed bar-graph model.
2024-07-14 Tweaks to jigs, coloured schematics, readme notes
2024-07-26 Pack PCB tweaks for 5V triggered FET/Relays, consolidating LED pins, and breaking out newly freed I/O pin. Re-jigged board layout and fixed some dimensions.
2024-08-18 Tweaked capacitor diameter in jigs
